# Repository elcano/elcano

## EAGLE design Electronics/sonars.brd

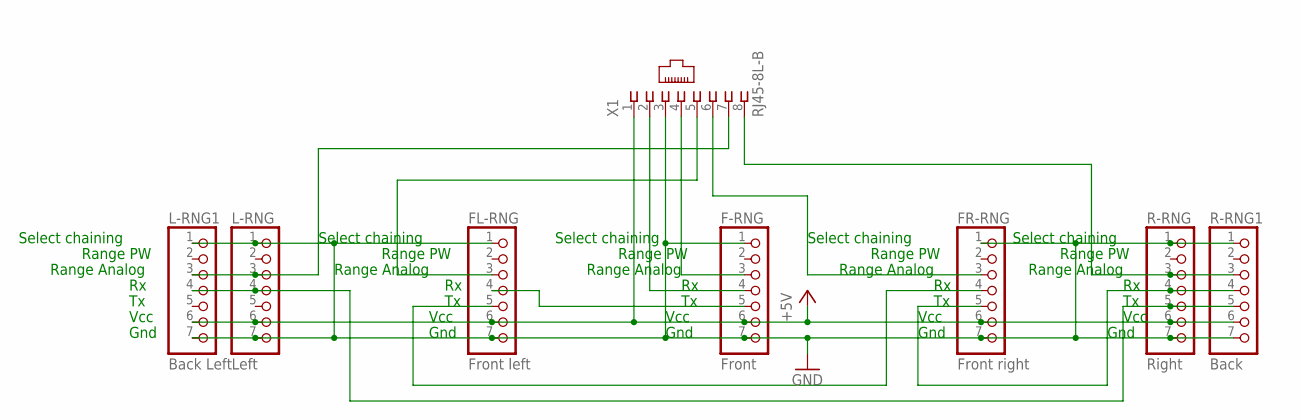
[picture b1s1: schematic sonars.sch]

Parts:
F-RNG: Front; 1X07
FL-RNG: Front left; 1X07
FR-RNG: Front right; 1X07
L-RNG: Left; 1X07
L-RNG1: Back Left; 1X07
R-RNG: Right; 1X07
R-RNG1: Back; 1X07
X1: RJ45-8L-B; RJ45-NO-SHIELD

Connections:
+5V: F-RNG.6, FL-RNG.6, FR-RNG.6, L-RNG.6, L-RNG1.6, R-RNG.6, R-RNG1.6, X1.1
CHN: F-RNG.4, X1.2
F>FL: F-RNG.5, FL-RNG.4
FL>FR: FL-RNG.5, FR-RNG.4
FL_RNG: FL-RNG.3, X1.5
FR>R: FR-RNG.5, R-RNG.4, R-RNG1.4
FR_RNG: FR-RNG.3, X1.6
F_RNG: F-RNG.3, X1.4
GND: F-RNG.1, F-RNG.7, FL-RNG.1, FL-RNG.7, FR-RNG.1, FR-RNG.7, L-RNG.1, L-RNG.7, L-RNG1.1, L-RNG1.7, R-RNG.1, R-RNG.7, R-RNG1.1, R-RNG1.7, X1.3
L_RNG: L-RNG.3, L-RNG1.3, X1.7
R>L: L-RNG.4, L-RNG1.4, R-RNG.5, R-RNG1.5
R_RNG: R-RNG.3, R-RNG1.3, X1.8

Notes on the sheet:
Select chaining
Range PW
Range Analog
Vcc
Gnd

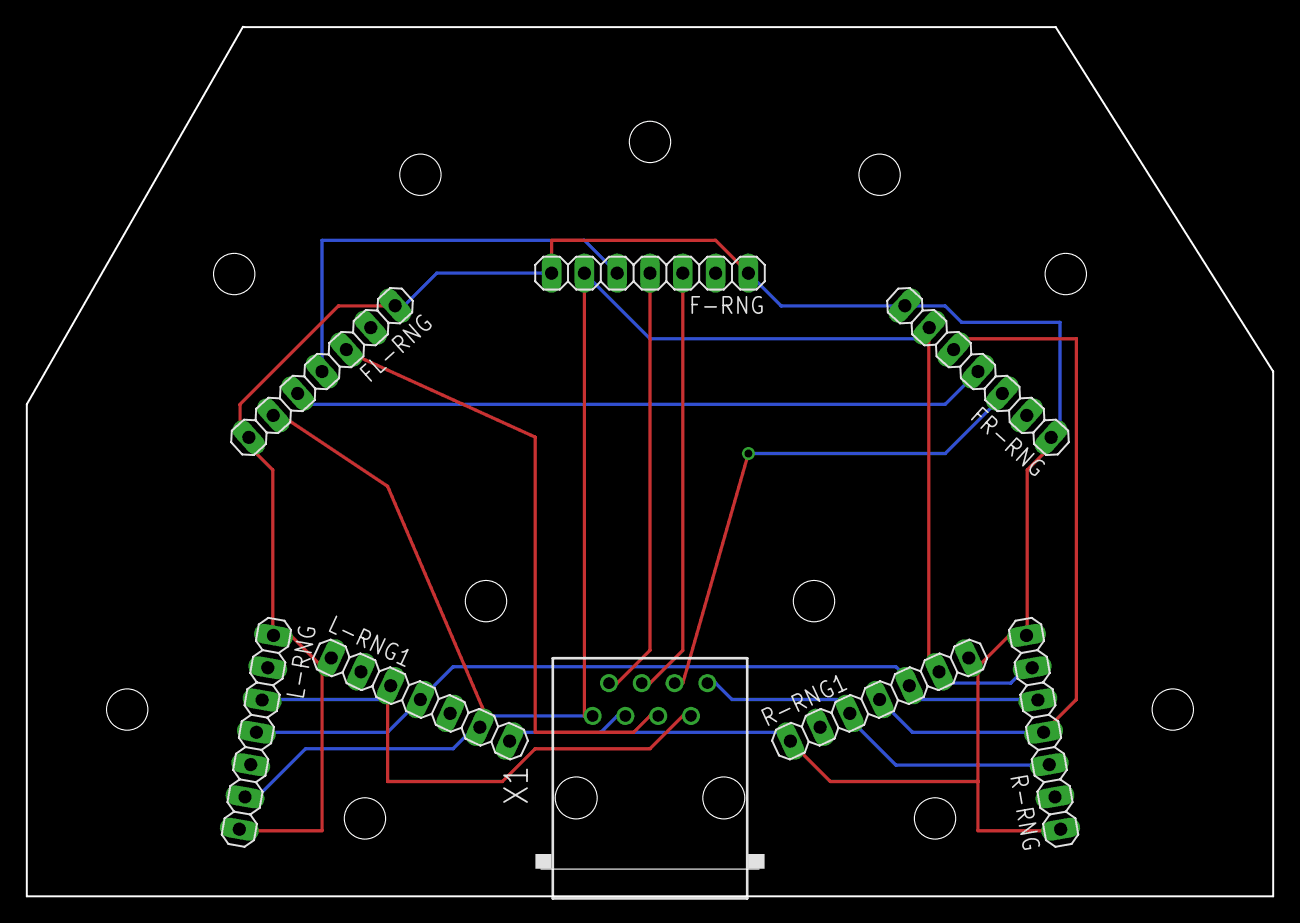
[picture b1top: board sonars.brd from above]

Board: 2 copper layers, 96.5 x 67.3 mm, 8 parts (0 on the bottom side), 12 nets.

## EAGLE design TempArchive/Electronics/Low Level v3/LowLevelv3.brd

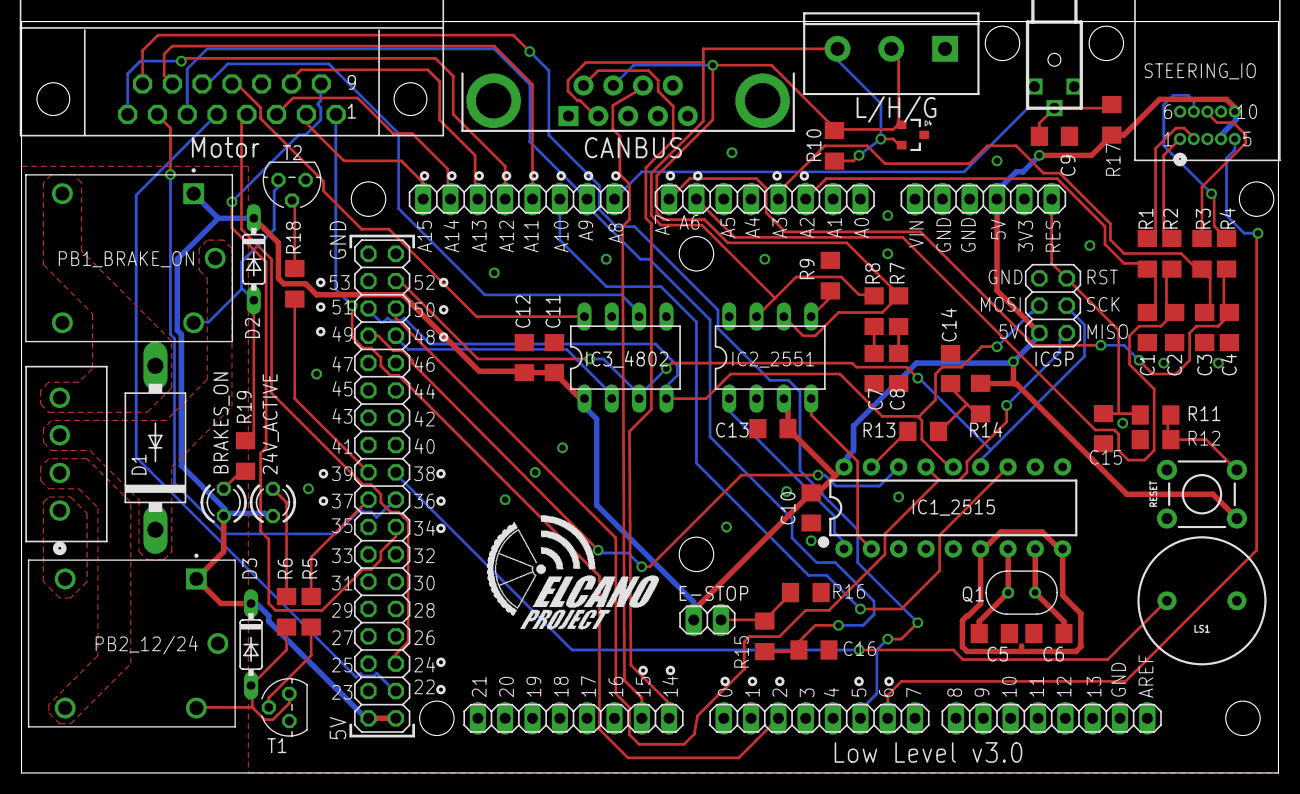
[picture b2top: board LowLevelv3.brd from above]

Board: 2 copper layers, 116.8 x 69.8 mm, 66 parts (0 on the bottom side), 62 nets.

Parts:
24V_ACTIVE: LED3MM
ADCH: Analog In 8-15; 1X08
ADCL: Analog In 0-7; 1X08
BRAKES_ON: LED3MM
C1, C2, C3, C4: 1uF; C1206
C5, C6: 33pF; C1206
C7, C8: 560pF; C1206
C9: 1 uF; C1206
C10, C11, C12, C13, C14: 0.1uF; C1206
C15, C16: 200nF; C1206
CANBUS: DB9 Plug; DB9
CAN_HEADER: SCREWTERMINAL-5MM-3
D1: 1N5400; DO201-15
D2, D3: 1N4148DO35-7; DO35-7
D4: PESD1CAN; SPARKFUN-DISCRETESEMI_SOT23-3
DIGITAL_0-7: Digital 0-7; 1X08
DIGITAL_8-13: Digital 8-13; 1X08
DIGITAL_14-21: Digital 14-21; 1X08
E-STOP: 1X02
IC1_2515: MCP2515; DIP18
IC2_2551: MCP2551DIL08; IC-PACKAGE_DIL08
IC3_4802: MCP4802; DIL08
ICSP: ICSP; 2X03
LS1: BUZZER-PTH; BUZZER-12MM
MEGA_EXPANSION: Digital 22-53; PINHEAD_2X18
PB1_BRAKE_ON, PB2_12/24: ORWH-SH-105D1F,000; TE_ORWH-SH-105D1F,000
POWER: 1X06
Q1: 16MHz; XTAL_ECS-160-20-46X
R1, R2, R3, R4, R9, R17: 4.7K; R1206
R5, R6, R13, R18, R19: 1K; R1206
R7, R8: 100; R1206
R10: 120; R1206
R11, R12, R15, R16: 10k; R1206
R14: 20K; R1206
RESET: MOMENTARY-SWITCH-SPST-PTH-6.0MM; TACTILE_SWITCH_PTH_6.0MM
STEERING_IO: 5-104069-4; CONN_5-104069-4_TYCO
T1, T2: 2N3904; TO92
X1: 284512-4
X3: Motor; 182-015-MALE
X4: CLICK; ODO_JACK

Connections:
5V: 24V_ACTIVE.A, BRAKES_ON.A, C10.1, C11.1, C12.1, C13.1, D2.C, D3.C, E-STOP.1, IC1_2515.18, IC2_2551.3, IC3_4802.1, ICSP.2, MEGA_EXPANSION.35, MEGA_EXPANSION.36, PB1_BRAKE_ON.1, PB2_12/24.1, POWER.3, R14.1, R17.1, RESET.1, STEERING_IO.4, STEERING_IO.10
12V: PB2_12/24.4, X1.1
24V: PB2_12/24.5, X1.2
BRAKE_ON: MEGA_EXPANSION.17, R18.1
BRAKE_PWM: DIGITAL_0-7.3, X3.1
BUZZER: LS1.+, MEGA_EXPANSION.18
CANH: CANBUS.7, CAN_HEADER.2, D4.1, IC2_2551.6, R7.2, R10.2
CANL: CANBUS.2, CAN_HEADER.3, D4.2, IC2_2551.7, R8.2, R10.1
CAN_INT: ADCH.6, IC1_2515.12
CAN_RXD: IC1_2515.2, IC2_2551.4
CAN_SS: IC1_2515.16, MEGA_EXPANSION.7
CAN_TXD: IC1_2515.1, IC2_2551.1
DACA: IC3_4802.8, X3.12
DACB: IC3_4802.6, X3.13
DAC_SS: IC3_4802.2, MEGA_EXPANSION.8
D_36: MEGA_EXPANSION.20, X3.7
EBIKECONTRL: ADCH.3, X3.10
ESTOP_INT: ADCH.7, C16.1, R15.1, X3.6
FWDSW: MEGA_EXPANSION.22, X3.9
GND: C1.2, C2.2, C3.2, C4.2, C5.2, C6.2, C7.2, C8.2, C9.2, C10.2, C11.2, C12.2, C13.2, C14.2, C15.2, C16.2, CANBUS.1, CANBUS.3, CAN_HEADER.1, D4.3, DIGITAL_8-13.7, IC1_2515.4, IC1_2515.5, IC1_2515.6, IC1_2515.9, IC2_2551.2, IC3_4802.5, IC3_4802.7, ICSP.6, LS1.-, MEGA_EXPANSION.1, MEGA_EXPANSION.2, POWER.4, POWER.5, R9.2, R12.2, R16.2, STEERING_IO.3, STEERING_IO.6, STEERING_IO.9, T1.3, T2.3, X3.11, X4.P$2, X4.P$3
HALLPHASEA: ADCH.1, X3.2
HALLPHASEB: ADCH.2, X3.3
HALLPHASEC: ADCH.4, X3.8
L_RET: R2.2, STEERING_IO.1
L_RTN_GND: ADCL.2, C2.1, R2.1
L_SENSE: ADCL.6, C1.1, R1.1
L_STR: R1.2, STEERING_IO.2
MISO: IC1_2515.15, ICSP.1, MEGA_EXPANSION.6
MOSI: IC1_2515.14, IC3_4802.4, ICSP.4, MEGA_EXPANSION.5
unnamed: R11.2, R12.1, RESET.3
unnamed: R5.2, T1.2
unnamed: D3.A, PB2_12/24.2, R6.1, T1.1
unnamed: C14.1, R13.2, R14.2
unnamed: 24V_ACTIVE.K, R6.2
unnamed: R18.2, T2.2
unnamed: E-STOP.2, R15.2, R16.1
unnamed: C7.1, R8.1
unnamed: C8.1, R7.1
unnamed: D2.A, PB1_BRAKE_ON.2, R19.1, T2.1
unnamed: BRAKES_ON.K, R19.2
unnamed: IC2_2551.5, R9.1
OSC1: C6.1, IC1_2515.8, Q1.2
OSC2: C5.1, IC1_2515.7, Q1.1
REGEN_ACTIVE: MEGA_EXPANSION.34, X3.5
RESET: C15.1, ICSP.5, POWER.1, R11.1
REVERSE: MEGA_EXPANSION.32, X3.4
RS: IC1_2515.17, R13.1
RX3: CANBUS.8, DIGITAL_14-21.7
R_RET: R4.2, STEERING_IO.7
R_RTN_GND: ADCL.1, C4.1, R4.1
R_SENSE: ADCL.5, C3.1, R3.1
R_STR: R3.2, STEERING_IO.8
SCK: IC1_2515.13, IC3_4802.3, ICSP.3, MEGA_EXPANSION.4
SOLENOID_COMMON: D1.A, PB1_BRAKE_ON.4, X1.4
SOLENOID_OUT: D1.C, PB1_BRAKE_ON.3, X1.3
SOLENOID_POWER: PB1_BRAKE_ON.5, PB2_12/24.3
SPEEDOMETER: ADCH.5, X3.14
STEER_SERVO_PWM: DIGITAL_0-7.7, STEERING_IO.5
TX3: CANBUS.6, DIGITAL_14-21.8
VOLTAGE_SWITCH: MEGA_EXPANSION.19, R5.1
WATCHDOG: DIGITAL_0-7.6, X3.15
WHEELROTATION: ADCH.8, C9.1, R17.2, X4.P$1

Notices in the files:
parts and their libraries:
SparkFun-Connectors: Licensing: CC v3.0 Share-Alike You are welcome to use this library for commercial purposes.
SparkFun-IC-Comms: Licensing: Creative Commons ShareAlike 4.0 International - https://creativecommons.org/licenses/by-sa/4.0
